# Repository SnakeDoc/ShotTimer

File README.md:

Shot Timer
===============================================================================

Copyright 2018 Jason Sipula

A sport shooting training aid that tracks individual shot times, splits and more.

_______________________________________________________________________________

Completed Hardware (LCD Screen disconnected for testing):

Circuit Schematic:

Traces:

Ground and Power Planes:

Bare Board (hand for scale reference):

Board Assembly:

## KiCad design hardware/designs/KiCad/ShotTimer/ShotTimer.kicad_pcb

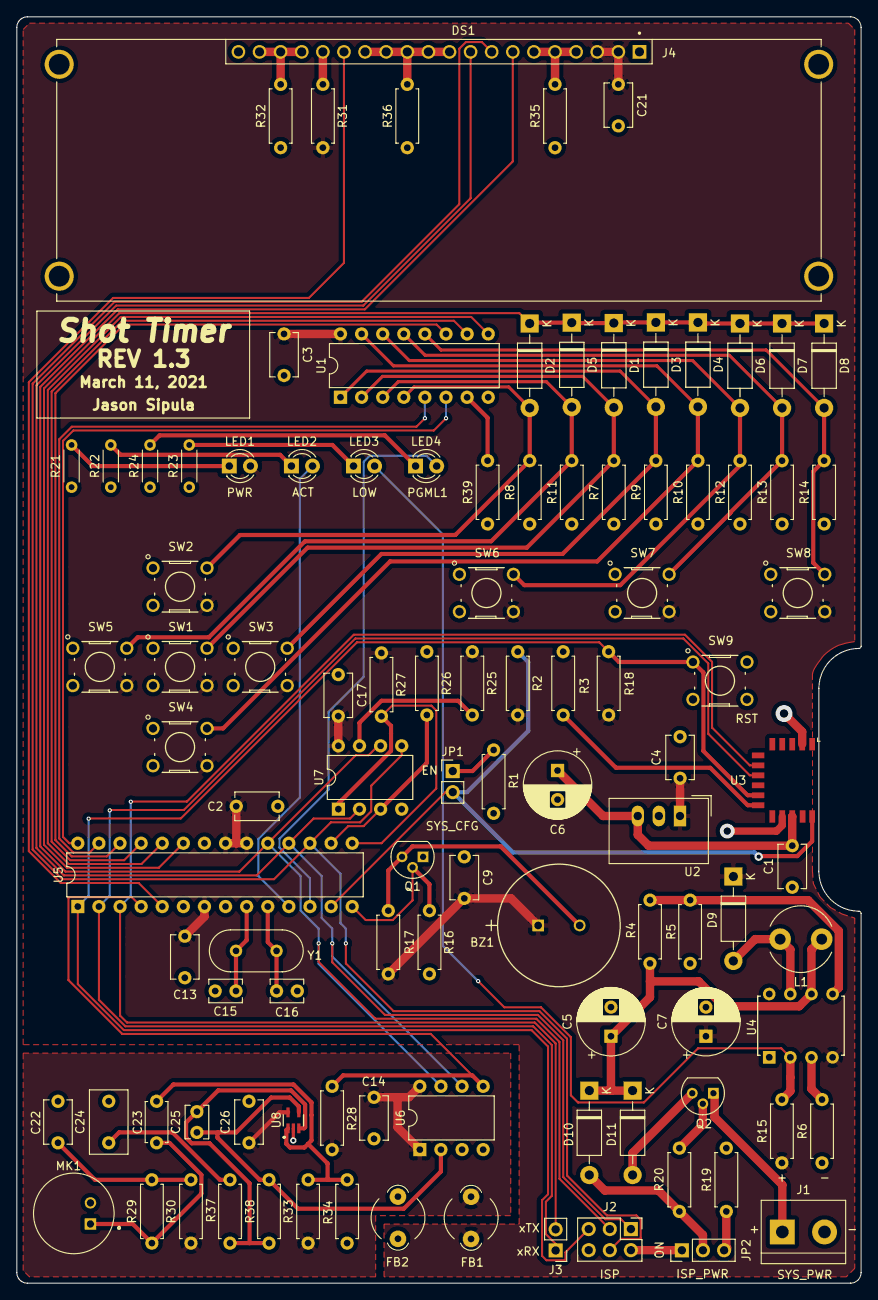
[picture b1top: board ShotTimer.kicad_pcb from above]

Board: 2 copper layers, 101.6 x 152.4 mm, 104 parts (0 on the bottom side), 65 nets.

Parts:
BZ1: Speaker; PS1420P02CT
C1, C2, C3, C4, C9, C13, C14, C17, C21, C22, C26: 0.1uF; C_Disc_D5.1mm_W3.2mm_P5.00mm
C5, C6, C7: 220uF; CP_Radial_D8.0mm_P3.50mm
C15, C16: 22pF; C_Disc_D3.8mm_W2.6mm_P2.50mm
C23: 10nF; C_Disc_D4.7mm_W2.5mm_P5.00mm
C24: 1uF; C_Disc_D7.5mm_W4.4mm_P5.00mm
C25: 100pF; C_Disc_D3.8mm_W2.6mm_P2.50mm
D1, D2, D3, D4, D5, D6, D7, D8, D9, D10, D11: 1N5817; D_DO-41_SOD81_P10.16mm_Horizontal
DS1: NHD-0420CW-SPI; NHD_NHD-0420CW-AG3
FB1, FB2: Ferrite_Bead; LairdTech_28C0236-0JW-10
J1: SYS_PWR; TerminalBlock_bornier-2_P5.08mm
J2: ISP; PinHeader_2x03_P2.54mm_Vertical
J3: SERIAL; PinHeader_1x02_P2.54mm_Vertical
JP1: SYS_CFG; PinHeader_1x02_P2.54mm_Vertical
JP2: ISP_PWR; PinHeader_1x03_P2.54mm_Vertical
L1: 33uH; L_Radial_D7.8mm_P5.00mm_Fastron_07HCP
LED1: Green; LED_D3.0mm
LED2, LED4: Yellow; LED_D3.0mm
LED3: Red; LED_D3.0mm
MK1: CMA-4544PF-W; MIC_CMA-4544PF-W
Q1: Q_NPN_EBC; TO-92
Q2: Q_PNP_CBE; TO-92
R1, R2, R3, R6, R7, R8, R9, R10, R11, R12, R13, R14, R16, R18, R19, R20, R25, R26, R27, R28, R31, R32, R35, R36, R37, R39: 10K; R_Axial_DIN0207_L6.3mm_D2.5mm_P7.62mm_Horizontal
R4: 316K 1%; R_Axial_DIN0207_L6.3mm_D2.5mm_P7.62mm_Horizontal
R5: 412K 1%; R_Axial_DIN0207_L6.3mm_D2.5mm_P7.62mm_Horizontal
R15, R38: 100K; R_Axial_DIN0207_L6.3mm_D2.5mm_P7.62mm_Horizontal
R17: 1K; R_Axial_DIN0207_L6.3mm_D2.5mm_P7.62mm_Horizontal
R21, R22, R23, R24: 330; R_Axial_DIN0204_L3.6mm_D1.6mm_P5.08mm_Horizontal
R29, R30: 2K; R_Axial_DIN0207_L6.3mm_D2.5mm_P7.62mm_Horizontal
R33, R34: 1M; R_Axial_DIN0207_L6.3mm_D2.5mm_P7.62mm_Horizontal
SW1, SW2, SW3, SW4, SW5, SW6, SW7, SW8: BTN; SW_B3F-10xx
SW9: Reset; SW_B3F-10xx
U1: CD74HC151E; DIP-16_W7.62mm
U2: TSR_1-2433; Converter_DCDC_TRACO_TSR-1_THT
U3: RN4871-I/RM140; Microchip_RN4871
U4: LT1303CN8-5#PBF; PDIP-8_N
U5: ATmega328P-PU; DIP-28_W7.62mm
U6: MCP3201; DIP-8_W7.62mm
U7: 25LC1024-I/P; DIP-8_W7.62mm
U8: MAX4466EXK; SOT65P210X110-5N
Y1: 16MHz; Crystal_HC49-U_Vertical

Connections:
+5V: BZ1.1, C2.2, C3.1, C4.1, C7.1, C9.2, C13.1, C17.2, C21.1, D9.1, DS1.2, DS1.3, FB1.2, LED1.2, R2.2, R15.1, R17.1, R18.1, R25.1, R27.2, R31.2, SW1.4, SW2.4, SW3.4, SW4.4, SW5.4, SW6.4, SW7.4, SW8.4, U1.16, U2.1, U4.4, U5.7, U5.20, U5.21, U7.8
+5VA: C14.1, C26.1, FB1.1, R28.2, R30.1, R33.1, U6.1, U6.8, U8.5
/ISP_PWR: J2.2, JP2.1
ACTIVITY: LED2.2, U5.11
BUTTON_PUSHED: D1.1, D2.1, D3.1, D4.1, D5.1, D6.1, D7.1, D8.1, U5.23
GND: C1.1, C2.1, C3.2, C4.2, C5.2, C6.2, C7.2, C9.1, C13.2, C15.1, C16.1, C17.1, C21.2, DS1.1, DS1.20, FB2.2, J1.2, J2.6, Q1.1, R1.1, R3.2, R5.1, R6.1, R7.1, R8.1, R9.1, R10.1, R11.1, R12.1, R13.1, R14.1, R16.2, R19.2, R21.1, R22.1, R23.1, R24.1, R26.1, R32.1, R35.1, R36.1, R39.1, SW9.3, U1.8, U2.2, U3.2, U3.13, U4.1, U4.8, U5.8, U5.22, U7.4
GNDA: C14.2, C22.2, C24.2, C26.2, FB2.1, MK1.2, R34.2, U6.3, U6.4, U8.2
ISP_RESET: J2.5, R18.2, SW9.1, U3.10, U5.1
LBO: LED3.2, R15.2, U4.2
MIC_AMP_OUT: C25.1, R38.1, U6.2, U8.4
MISO: DS1.9, J2.1, U5.18, U6.6, U7.2
MOSI: DS1.8, J2.4, U5.17, U7.5
unnamed: BZ1.2, Q1.3, R17.2
unnamed: C1.2, C6.1, U2.3, U3.14
unnamed: C15.2, U5.9, Y1.1
unnamed: C16.2, U5.10, Y1.2
unnamed: C22.1, R29.1, R30.2
unnamed: C23.1, R33.2, R34.1, U8.1
unnamed: C23.2, MK1.1, R29.2
unnamed: C24.1, R37.1
unnamed: C25.2, R37.2, R38.2, U8.3
unnamed: D1.2, R7.2, SW1.2, U1.2
unnamed: D2.2, R8.2, SW2.2, U1.4
unnamed: D3.2, R9.2, SW3.2, U1.1
unnamed: D4.2, R10.2, SW4.2, U1.15
unnamed: D5.2, R11.2, SW5.2, U1.3
unnamed: D6.2, R12.2, SW6.2, U1.14
unnamed: D7.2, R13.2, SW7.2, U1.13
unnamed: D8.2, R14.2, SW8.2, U1.12
unnamed: D9.2, L1.2, U4.7
unnamed: D10.2, JP2.2, R20.1
unnamed: D11.2, Q2.3
unnamed: DS1.4, DS1.5, DS1.6, R35.2
unnamed: DS1.10, DS1.11, DS1.12, DS1.13, DS1.14, R36.2
unnamed: DS1.16, R31.1
unnamed: DS1.17, DS1.18, DS1.19, R32.2
unnamed: JP1.1, R1.2
unnamed: JP2.3, R19.1
unnamed: LED1.1, R21.2
unnamed: LED2.1, R22.2
unnamed: LED3.1, R23.2
unnamed: LED4.1, R24.2
unnamed: Q2.2, R20.2
unnamed: R3.1, U3.11
unnamed: R4.1, R5.2, U4.5
unnamed: R6.2, U4.3
unnamed: R25.2, U7.7
unnamed: R39.2, U1.7
PGML1: LED4.2, U5.12
PGM_RF: JP1.2, R2.1, U3.16, U5.13
PWR: C5.1, D10.1, D11.1, L1.1, R4.2, U4.6
RX: J3.1, U3.8, U5.2
S0: U1.11, U5.26
S1: U1.10, U5.25
S2: U1.9, U5.24
SCK: DS1.7, J2.3, U5.19, U6.7, U7.6
SPEAKER_PWM: Q1.2, R16.1, U5.14
SS_ADC: R28.1, U5.4, U6.5
SS_DS: DS1.15, U5.5
SS_EEPROM: R27.1, U5.15, U7.1
SYS_PWR: J1.1, Q2.1
TX: J3.2, U3.7, U5.3
Write_Protection: R26.2, U5.16, U7.3
Y: U1.5, U5.27
~Y: U1.6, U5.28

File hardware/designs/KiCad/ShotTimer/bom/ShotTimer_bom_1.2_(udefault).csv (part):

Component,Quantity,Reference Designator,Customer Reference,Value,Quantity Per PCB,Digi-Key Part Number,Manufacturer,Manufacturer Part Number,Footprint,Description,Datasheet,Part,Mouser Part Number,Build Quantity,References,UserGuide
1, 3, BZ1, BZ1,Speaker,1,445-2526-1-ND,TDK Corporation,PS1420P02CT,PS1420P02CT,"Buzzer, polarized",https://product.tdk.com/info/en/catalog/datasheets/piezoelec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,Buzzer,810-PS1420P02CT,3,BZ1,
2, 6, C15 C16, C15 C16,22pF,2,BC1005CT-ND,Vishay Beyschlag/Draloric/BC Components,K220J15C0GF5TL2,C_Disc_D3.8mm_W2.6mm_P2.50mm,Unpolarized capacitor,https://www.vishay.com/docs/45171/kseries.pdf,C,594-K220J15C0GF5TL2,6,C15 C16,
3, 3, C25, C25,100pF,1,BC1013CT-ND,Vishay Beyschlag/Draloric/BC Components,K101J15C0GF5TL2,C_Disc_D3.8mm_W2.6mm_P2.50mm,Unpolarized capacitor,https://www.vishay.com/docs/45171/kseries.pdf,C,594-K101J15C0GF5TL2,3,C25,
4, 3, C23, C23,10nF,1,445-173474-1-ND,TDK Corporation,FG28C0G1H103JNT06,C_Disc_D4.7mm_W2.5mm_P5.00mm,Unpolarized capacitor,https://product.tdk.com/info/en/catalog/datasheets/leadmlcc_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,C,810-FG28C0G1H103JNT6,3,C23,
5, 33, C1 C2 C3 C4 C9 C13 C14 C17 C21 C22 C26, C1 C2 C3 C4 C9 C13 C14 C17 C21 C22 C26,0.1uF,11,399-13932-ND,KEMET,C322C104J5R5TA,C_Disc_D5.1mm_W3.2mm_P5.00mm,Unpolarized capacitor,https://content.kemet.com/datasheets/KEM_C1050_GOLDMAX_X7R.pdf,C,80-C322C104J5R,33,C1 C2 C3 C4 C9 C13 C14 C17 C21 C22 C26,
6, 3, C24, C24,1uF,1,399-13901-ND,KEMET,C330C105J5R5TA,C_Disc_D7.5mm_W4.4mm_P5.00mm,Unpolarized capacitor,https://product.tdk.com/info/en/catalog/datasheets/leadmlcc_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,C,80-C330C105J5R,3,C24,
7, 9, C5 C6 C7, C5 C6 C7,220uF,3,P16296-ND,Panasonic Electronic Components,16SEPC220MD,CP_Radial_D8.0mm_P3.50mm,"Polarized capacitor, US symbol",https://industrial.panasonic.com/cdbs/www-data/pdf/AAB8000/A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,CP1,667-16SEPC220MD,9,C5 C6 C7,
8, 33, D1 D2 D3 D4 D5 D6 D7 D8 D9 D10 D11, D1 D2 D3 D4 D5 D6 D7 D8 D9 D10 D11,1N5817,11,497-4547-1-ND,STMicroelectronics,1N5817,D_DO-41_SOD81_P10.16mm_Horizontal,"20V 1A Schottky Barrier Rectifier Diode, DO-41",https://www.st.com/content/ccc/resource/technical/document/d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,1N5817,511-1N5817,33,D1 D2 D3 D4 D5 D6 D7 D8 D9 D10 D11,
9, 3, DS1, DS1,NHD-0420CW-SPI,1,NHD-0420CW-AB3-ND,Newhaven Display Intl,NHD-0420CW-AB3,NHD_NHD-0420CW-AG3,"20x4 Character LCD Display Module Passive 5 x 8 Dots OLED Parallel, 8-Bit, I²C, SPI",https://www.newhavendisplay.com/specs/NHD-0420CW-AB3.pdf,NHD-0420CW-SPI,763-NHD-0420CW-AB3,3,DS1,https://www.newhavendisplay.com/app_notes/US2066.pdf
10, 6, FB1 FB2, FB1 FB2,Ferrite_Bead,2,240-2493-ND,Laird-Signal Integrity Products,28C0236-0JW-10,LairdTech_28C0236-0JW-10,Ferrite bead,https://media.digikey.com/pdf/Data%20Sheets/Steward%20PDFs/P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,Ferrite_Bead,875-28C0236-0JW-10,6,FB1 FB2,
11, 3, J2, J2,ISP,1,2057-PH2-06-UA-ND,Adam Tech,PH2-06-UA,PinHeader_2x03_P2.54mm_Vertical,"Generic connector, double row, 02x03, odd/even pin numbering scheme (row 1 odd numbers, row 2 even numbers), script generated (kicad-library-utils/schlib/autogen/connector/)",~,Conn_02x03_Odd_Even,,3,J2,
12, 3, J3, J3,SERIAL,1,2057-PH1-02-UA-ND,Adam Tech,PH1-02-UA,PinHeader_1x02_P2.54mm_Vertical,"Generic connector, single row, 01x02, script generated (kicad-library-utils/schlib/autogen/connector/)",~,Conn_01x02,,3,J3,
13, 3, J1, J1,SYS_PWR,1,732-10955-ND,Würth Elektronik,691137710002,TerminalBlock_bornier-2_P5.08mm,"Generic screw terminal, single row, 01x02, script generated (kicad-library-utils/schlib/autogen/connector/)",https://www.we-online.de/katalog/datasheet/691137710002.pdf,Screw_Terminal_01x02,710-691137710002,3,J1,
14, 3, JP2, JP2,ISP_PWR,1,2057-PH1-03-UA-ND,Adam Tech,PH1-03-UA,PinHeader_1x03_P2.54mm_Vertical,"Dual jumper, normally closed",~,Jumper_NC_Dual,,3,JP2,
15, 3, JP1, JP1,SYS_CFG,1,2057-PH1-02-UA-ND,Adam Tech,PH1-02-UA,PinHeader_1x02_P2.54mm_Vertical,"Jumper, 2-pole, open",~,Jumper_2_Open,,3,JP1,
16, 3, L1, L1,33uH,1,308-2103-ND,Sumida America Components Inc.,RCH895NP-330K,L_Radial_D7.8mm_P5.00mm_Fastron_07HCP,Inductor,http://products.sumida.com/products/pdf/RCH-895.pdf,L,851-RCH895NP-330K,3,L1,
17, 3, LED1, LED1,Green,1,732-5007-ND,Würth Elektronik,151031VS04000,LED_D3.0mm,Light emitting diode,https://www.we-online.de/katalog/datasheet/151031VS04000.pdf,LED,710-151031VS04000,3,LED1,
18, 3, LED3, LED3,Red,1,732-5005-ND,Würth Elektronik,151031SS04000,LED_D3.0mm,Light emitting diode,https://katalog.we-online.de/led/datasheet/151031SS04000.pdf,LED,710-151031SS04000,3,LED3,
19, 6, LED2 LED4, LED2 LED4,Yellow,2,732-5010-ND,Würth Elektronik,151031YS06000,LED_D3.0mm,Light emitting diode,https://www.we-online.de/katalog/datasheet/151031YS06000.pdf,LED,710-151031YS06000,6,LED2 LED4,
20, 3, MK1, MK1,CMA-4544PF-W,1,102-1721-ND,CUI Devices,CMA-4544PF-W,MIC_CMA-4544PF-W,,https://www.cuidevices.com/product/resource/cma-4544pf-w.pdf,CMA-4544PF-W,490-CMA-4544PF-W,3,MK1,
21, 3, Q1, Q1,Q_NPN_EBC,1,KSP2222ABUFS-ND,ON Semiconductor,KSP2222ABU,TO-92,"NPN transistor, emitter/base/collector",https://www.onsemi.com/pub/Collateral/KSP2222A-D.PDF,Q_NPN_EBC,512-KSP2222ABU,3,Q1,
22, 3, Q2, Q2,Q_PNP_CBE,1,PN2907-ND,ON Semiconductor,PN2907BU,TO-92,"PNP transistor, collector/base/emitter",https://media.digikey.com/pdf/Data%20Sheets/Fairchild%20PDFs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,Q_PNP_CBE,512-PN2907BU,3,Q2,
23, 12, R21 R22 R23 R24, R21 R22 R23 R24,330,4,S330CACT-ND,Stackpole Electronics Inc,RNMF14FTC330R,R_Axial_DIN0204_L3.6mm_D1.6mm_P5.08mm_Horizontal,"Resistor, US symbol",https://www.seielect.com/catalog/sei-rnf_rnmf.pdf,R_US,,12,R21 R22 R23 R24,
24, 3, R17, R17,1K,1,RNF14FTD1K00CT-ND,Stackpole Electronics Inc,RNF14FTD1K00,R_Axial_DIN0207_L6.3mm_D2.5mm_P7.62mm_Horizontal,"Resistor, US symbol",https://www.seielect.com/catalog/sei-rnf_rnmf.pdf,R_US,,3,R17,
25, 6, R29 R30, R29 R30,2K,2,RNF14FTD2K00CT-ND,Stackpole Electronics Inc,RNF14FTD2K00,R_Axial_DIN0207_L6.3mm_D2.5mm_P7.62mm_Horizontal,"Resistor, US symbol",https://www.seielect.com/catalog/sei-rnf_rnmf.pdf,R_US,,6,R29 R30,
26, 78, R1 R2 R3 R6 R7 R8 R9 R10 R11 R12 R13 R14 R16 R18 R19 R20 R25 R26 R27 R28 R31 R32 R35 R36 R37 R39, R1 R2 R3 R6 R7 R8 R9 R10 R11 R12 R13 R14 R16 R18 R19 R20 R25 R26 R27 R28 R31 R32 R35 R36 R37 R39,10K,26,RNF14FTD10K0CT-ND,Stackpole Electronics Inc,RNF14FTD10K0,R_Axial_DIN0207_L6.3mm_D2.5mm_P7.62mm_Horizontal,"Resistor, US symbol",https://www.seielect.com/catalog/sei-rnf_rnmf.pdf,R_US,,78,R1 R2 R3 R6 R7 R8 R9 R10 R11 R12 R13 R14 R16 R18 R19 R20 R25 R26 R27 R28 R31 R32 R35 R36 R37 R39,
27, 6, R15 R38, R15 R38,100K,2,RNF14FTD100KCT-ND,Stackpole Electronics Inc,RNF14FTD100K,R_Axial_DIN0207_L6.3mm_D2.5mm_P7.62mm_Horizontal,"Resistor, US symbol",https://www.seielect.com/catalog/sei-rnf_rnmf.pdf,R_US,,6,R15 R38,
28, 6, R33 R34, R33 R34,1M,2,RNF14FTD1M00CT-ND,Stackpole Electronics Inc,RNF14FTD1M00,R_Axial_DIN0207_L6.3mm_D2.5mm_P7.62mm_Horizontal,"Resistor, US symbol",https://www.seielect.com/catalog/sei-rnf_rnmf.pdf,R_US,,6,R33 R34,
29, 3, R4, R4,316K 1%,1,RNF14FTD316KCT-ND,Stackpole Electronics Inc,RNF14FTD316K,R_Axial_DIN0207_L6.3mm_D2.5mm_P7.62mm_Horizontal,"Resistor, US symbol",https://www.seielect.com/catalog/sei-rnf_rnmf.pdf,R_US,,3,R4,
30, 3, R5, R5,412K 1%,1,RNF14FTD412KCT-ND,Stackpole Electronics Inc,RNF14FTD412K,R_Axial_DIN0207_L6.3mm_D2.5mm_P7.62mm_Horizontal,"Resistor, US symbol",https://www.seielect.com/catalog/sei-rnf_rnmf.pdf,R_US,,3,R5,
31, 24, SW1 SW2 SW3 SW4 SW5 SW6 SW7 SW8, SW1 SW2 SW3 SW4 SW5 SW6 SW7 SW8,BTN,8,SW400-ND,Omron Electronics Inc-EMC Div,B3F-1000,SW_B3F-10xx,"Push button switch, generic, two pins",https://omronfs.omron.com/en_US/ecb/products/pdf/en-b3f.pdf,SW_Push_2-4,653-B3F-1000,24,SW1 SW2 SW3 SW4 SW5 SW6 SW7 SW8,
32, 3, SW9, SW9,Reset,1,SW950-ND,Omron Electronics Inc-EMC Div,B3F-1006,SW_B3F-10xx,"Push button switch, generic, two pins",https://omronfs.omron.com/en_US/ecb/products/pdf/en-b3f.pdf,SW_Push_1-3,653-B3F-1006,3,SW9,
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
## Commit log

2018-08-01 Add a confidential license for now...
2018-08-01 Add debug logging capabilities
2018-08-01 Will have the main.cpp hook into the program runtime, launching the main app
2018-08-01 Use the new shottimer.h hooks, and point out this file is essentially a standard run-of-the-mill Arduino project main.cpp file
2018-08-07 VS Code seems to really, really want to ignore this file... so I guess let it. (It keeps adding this line to the bottom of my gitignore every time I restart VS Code...)
2018-08-07 Revamped debug system, now it's header-only, and has better utility by providing an option to print milliseconds, function name, file name and line number.
2018-08-07 Remove this define for debug logging and move it into debug.h to keep as much of the debugging stuff together as possible.
2018-08-07 Include the new debug header, and make sure it's initialized if we've defined debug logging to be enabled. Also included a test control loop for testing...
2018-08-07 Not having the init_debug() implementation in a separate cpp source file was making use of the file difficult with multiple files including the debug header.
2018-08-07 Add headers to header file, and add new sample code
2018-08-07 interface for audio device drivers, such as mic's and amps
2018-08-07 Initial driver implementation - borrowed from adafruit sample code
2020-07-25 update gitignore
2020-07-25 update tracked proj files
2020-07-26 reorg into C++ project, refactor some package stuff
2020-07-26 lib dir
2020-07-26 too many advantages of macro version of logging... Mainly, it can log the correct filename and line number a lot easier
2020-07-26 renamed file
2020-07-26 store logging strings on flash mem
2020-07-27 inherit audiodriver
2020-07-27 Rebuilt queue, use z-scores to detect placement in sound ditribution
2020-07-27 tuned to reject detected samples, so we don't pollute our levels. tune sample window
2020-07-27 cleanup
2020-07-27 lame attempt at echo bounceback rejection
2020-07-27 reject all readings below decibel threshold value, but record their value to enable background noise level smoothing.
2020-07-27 specify db level
2020-07-27 Breadboard design so far
2020-07-28 update design
2020-09-09 sync fritzing designs... slacker
2020-09-09 sync changes... including refactor, template the circular queue so we can accept generic types, test various methods for calculating dbA from our audio sensor, but nothing is right so far. have a few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
2020-09-09 C++ify this basic data type
2020-09-09 use new simplified data type
2020-09-09 not working linked list. doing it the hard, err... C++ way...
2020-09-11 down and dirty...
2020-12-14 Atmel/Microchip Studio is based on Visual Studio
2020-12-14 Port project to Atmel (Microchip) Studio facilitate hardware debugging using Xplained
2021-01-20 sync - new display driver, refactor, compiler error squashing...
2021-01-21 it compiles!
2021-01-21 templates make pure virtual functions and interfaces... challenging.
2021-01-21 create manager and driver objects
2021-01-24 refactor
2021-02-15 update gitignore for Kicad
2021-02-15 KiCad Schematic for ShotTimer
2021-02-25 Rev 1.1 - optimized parts, updated BOM, reorged kicad part deps, started PCB layout
2021-03-06 initial pcb layout, bump to rev 1.2 remove 10uF caps, tidy up
2021-03-12 PCB REV1.3 - first design sent to fab.
2021-03-25 refactor messy hw folder
2021-03-25 allow tracking of finalized boms
2021-03-25 final boms for hw versions
2021-03-25 old fritzing start of a design... saving into git just for funsies
2021-03-25 basic driver for MC3201 ADC via SPI communication
2021-03-27 things...
2021-03-27 remove platformio stuff
2021-03-27 move .git up a level to match AS7/VS proj structure
2021-03-27 remove and ignore VS user files
2021-03-27 move hardware folder to tld
2021-03-27 refactor project layout
2021-03-28 standardize include format, fix startup functions
2021-03-28 refactor package structure
2021-04-25 squash compiler complaint, and follow private var conventions
2021-04-25 start of the US2066 SPI driver implementation
2021-05-02 fix compiler errors and missing cursor position reset
2021-05-02 finished basic US2066 driver, untested on device.
2025-08-14 open source this repo
2025-08-14 update readme for open sourcing repo

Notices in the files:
parts and their libraries:
Copyright 2016 Accelerated Designs. All rights reserved.
